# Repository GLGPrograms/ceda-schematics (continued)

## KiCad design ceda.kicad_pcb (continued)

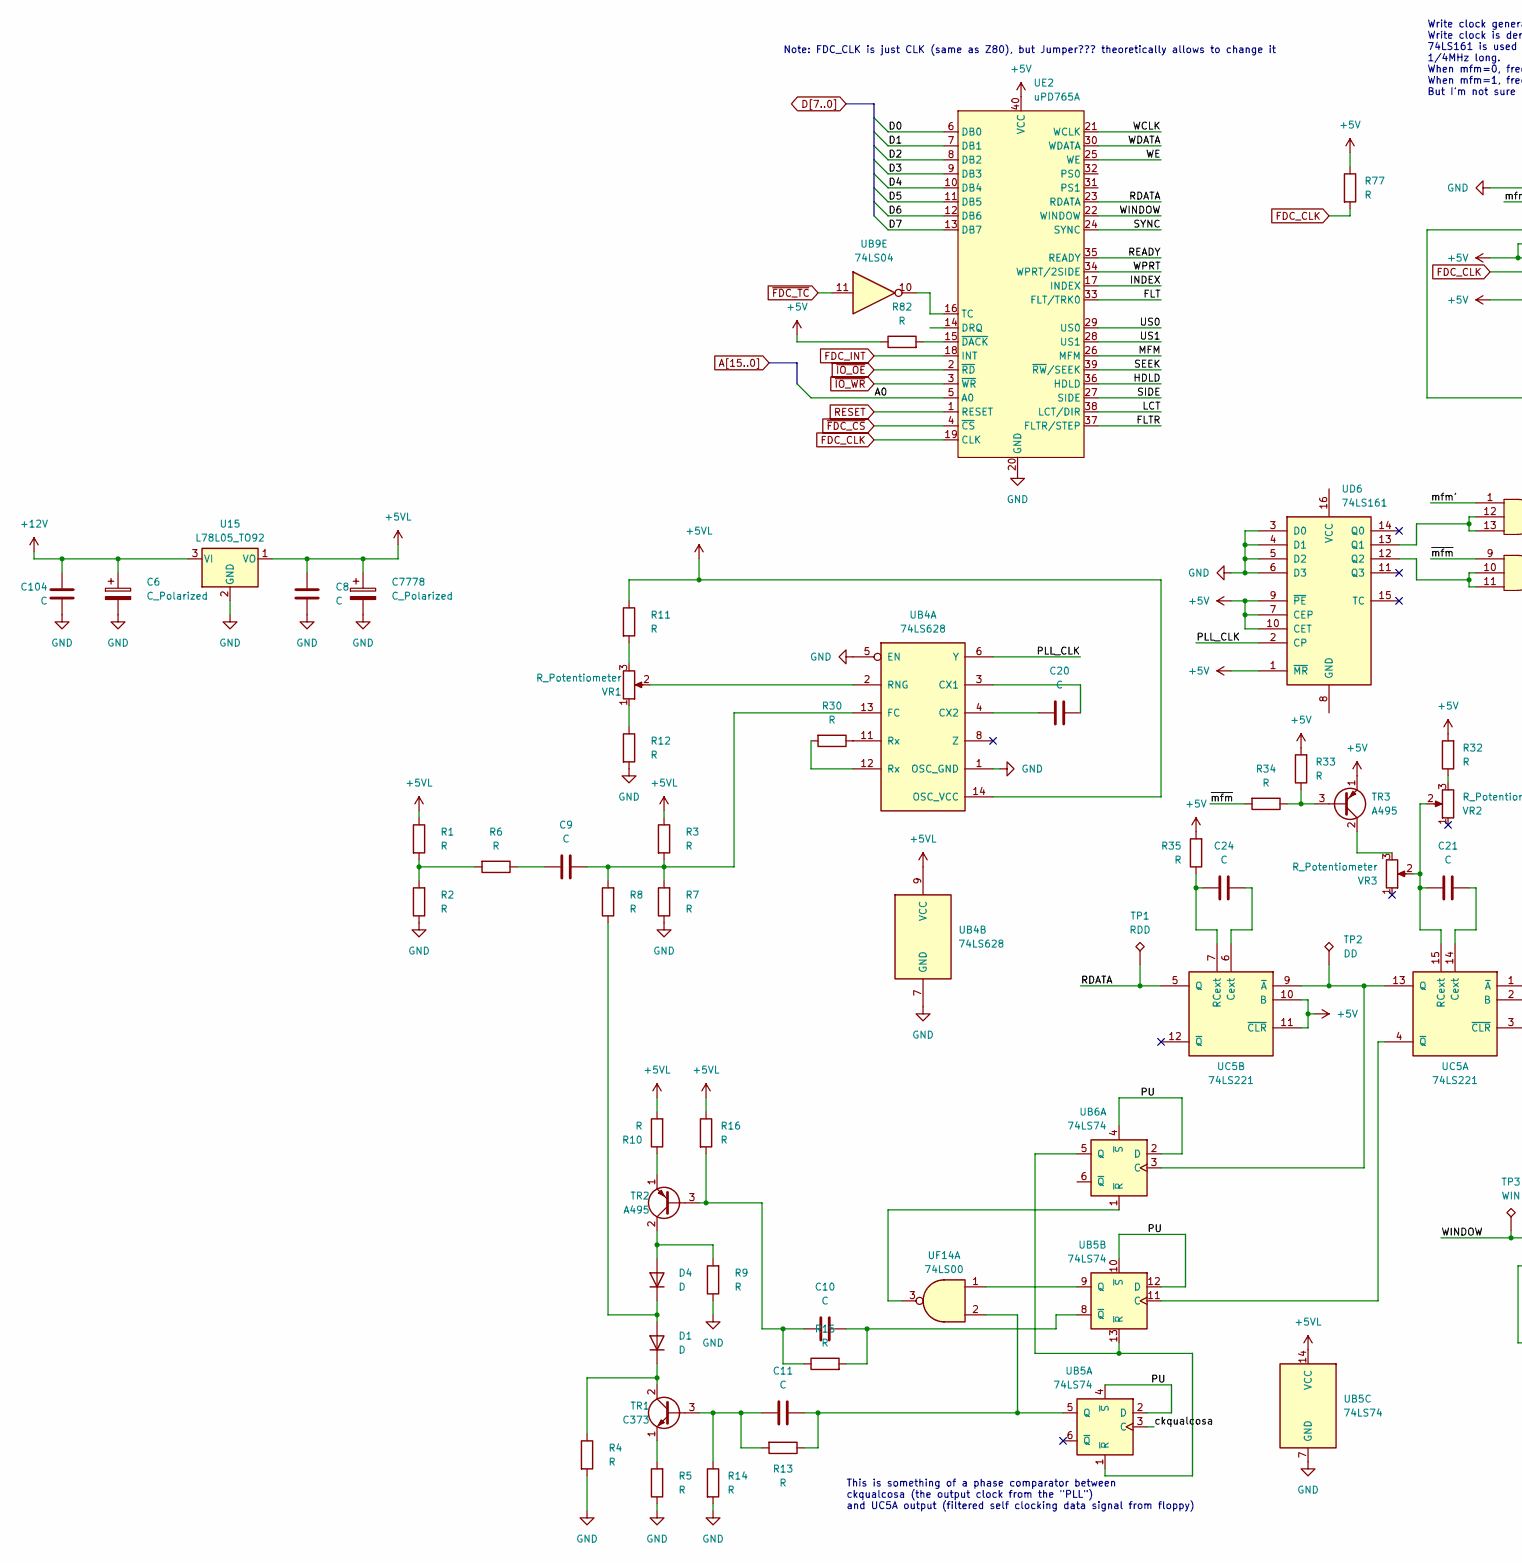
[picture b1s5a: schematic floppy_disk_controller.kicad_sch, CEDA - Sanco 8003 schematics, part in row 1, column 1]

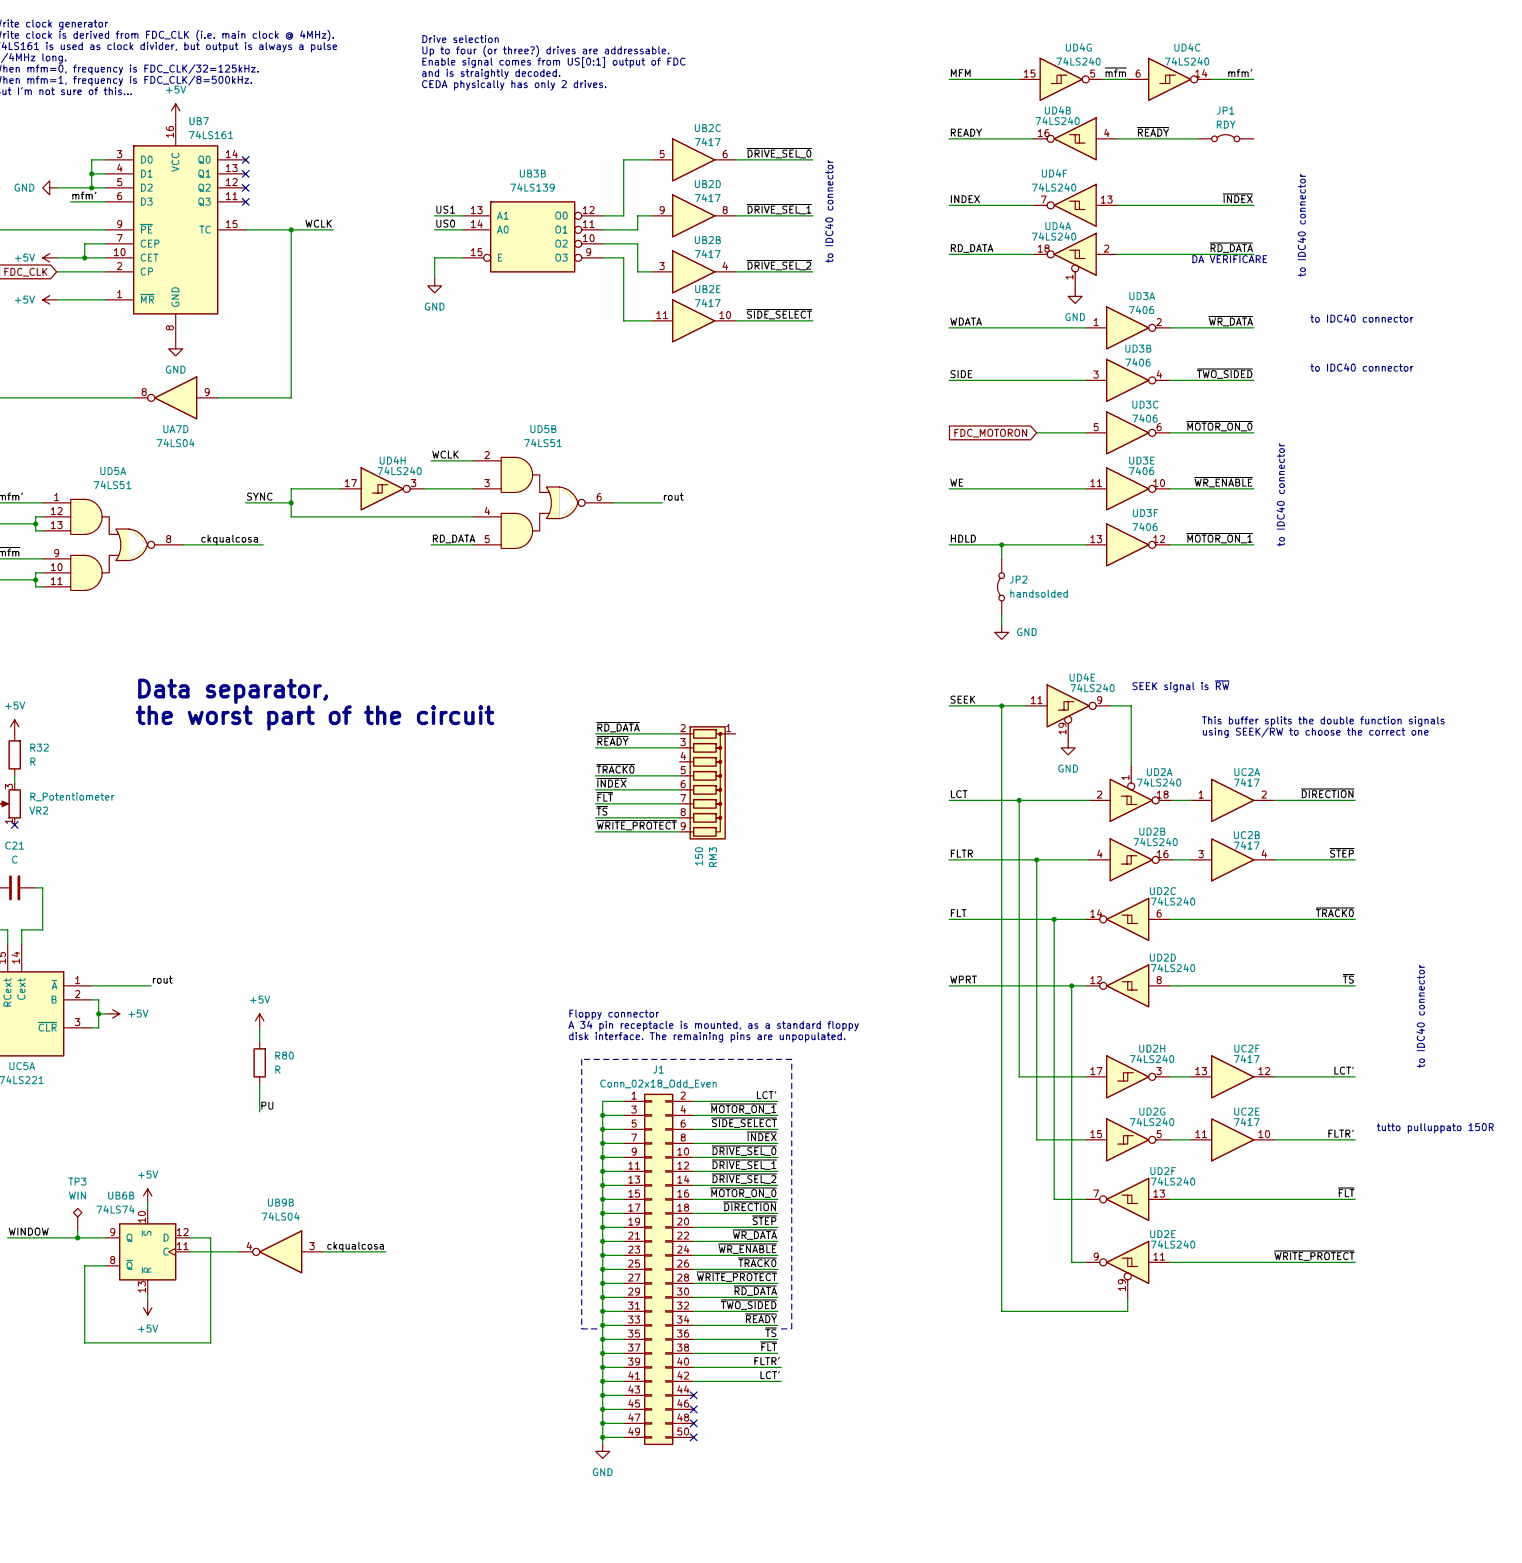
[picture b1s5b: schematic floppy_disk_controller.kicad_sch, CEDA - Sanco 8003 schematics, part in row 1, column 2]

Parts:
C6, C7778: C_Polarized; CP_Radial_D5.0mm_P2.50mm
C8, C9, C10, C11, C20, C21, C24, C104: C; C_Disc_D4.3mm_W1.9mm_P5.00mm
D1, D4: D; D_A-405_P5.08mm_Vertical_KathodeUp
J1: Conn_02x18_Odd_Even; IDC-Header_2x25_P2.54mm_Vertical
JP1: RDY; PinHeader_2x01_P2.54mm_Vertical
JP2: handsolded
R1, R2, R3, R4, R5, R6, R7, R8, R9, R10, R11, R12, R13, R14, R15, R16, R30, R32, R33, R34, R35, R80, R82: R; R_Axial_DIN0204_L3.6mm_D1.6mm_P5.08mm_Vertical
R77: R; R_Axial_DIN0309_L9.0mm_D3.2mm_P12.70mm_Horizontal
RM3: 150; R_Array_SIP9
TP1: RDD; TestPoint_Plated_Hole_D2.0mm
TP2: DD; TestPoint_Plated_Hole_D2.0mm
TP3: WIN; TestPoint_Plated_Hole_D2.0mm
TR1: C373; TO-92_Inline_Wide
TR2, TR3: A495; TO-92_Inline_Wide
U15: L78L05_TO92; TO-92_Inline_Wide
UA7: 74LS04; DIP-14_W7.62mm
UB2: 7417; DIP-14_W7.62mm
UB3: 74LS139; DIP-16_W7.62mm
UB4: 74LS628; DIP-14_W7.62mm
UB5, UB6: 74LS74; DIP-14_W7.62mm
UB7: 74LS161; DIP-16_W7.62mm
UB9: 74LS04; DIP-14_W7.62mm
UC2: 7417; DIP-14_W7.62mm
UC5: 74LS221; DIP-16_W7.62mm
UD2, UD4: 74LS240; DIP-20_W7.62mm
UD3: 7406; DIP-14_W7.62mm
UD5: 74LS51; DIP-14_W7.62mm
UD6: 74LS161; DIP-16_W7.62mm
UE2: uPD765A; DIP-40_W15.24mm
UF14: 74LS00; DIP-14_W7.62mm
VR1, VR2, VR3: R_Potentiometer; Round_Trimmer

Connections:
+5V: R32.2, R33.2, R35.2, R77.1, R80.2, R82.1, TR3.1 (E), UB6.10 (~S), UB6.13 (~R), UB7.1 (~MR), UB7.7 (CEP), UB7.10 (CET), UB7.16 (VCC), UC5.2 (B), UC5.3 (~CLR), UC5.10 (B), UC5.11 (~CLR), UD6.1 (~MR), UD6.7 (CEP), UD6.9 (~PE), UD6.10 (CET), UE2.40 (VCC); also elsewhere on the board
+5VL: C8.1, C7778.1, R1.1, R3.1, R10.2, R11.1, R16.1, U15.1 (VO), UB4.9 (VCC), UB4.14 (OSC_VCC), UB5.14 (VCC)
+12V: C6.1, C104.1, U15.3 (VI); also elsewhere on the board
/FloppyDiskController/FLT: UD2.7, UD2.14, UE2.33 (FLT/TRK0)
/FloppyDiskController/FLTR: UD2.4, UD2.15, UE2.37 (FLTR/STEP)
/FloppyDiskController/FLTR': J1.40, UC2.10
/FloppyDiskController/HDLD: JP2.2 (B), UD3.13, UE2.36 (HDLD)
/FloppyDiskController/INDEX: UD4.7, UE2.17 (INDEX)
/FloppyDiskController/LCT: UD2.2, UD2.17, UE2.38 (LCT/DIR)
/FloppyDiskController/LCT': J1.2, J1.42, UC2.12
/FloppyDiskController/MFM: UD4.15, UE2.26 (MFM)
/FloppyDiskController/PLL_CLK: UB4.6 (Y), UD6.2 (CP)
/FloppyDiskController/PU: R80.1, UB5.2 (D), UB5.4 (~S), UB5.10 (~S), UB5.12 (D), UB6.2 (D), UB6.4 (~S)
/FloppyDiskController/RDATA: TP1.1, UC5.5 (Q), UE2.23 (RDATA)
/FloppyDiskController/RD_DATA: UD4.18, UD5.5
/FloppyDiskController/READY: UD4.16, UE2.35 (READY)
/FloppyDiskController/SEEK: UD2.19, UD4.11, UE2.39 (~RW/SEEK)
/FloppyDiskController/SIDE: UD3.3, UE2.27 (SIDE)
/FloppyDiskController/SYNC: UD4.17, UD5.4, UE2.24 (SYNC)
/FloppyDiskController/US0: UB3.14 (A0), UE2.29 (US0)
/FloppyDiskController/US1: UB3.13 (A1), UE2.28 (US1)
/FloppyDiskController/WCLK: UA7.9, UB7.15 (TC), UD5.2, UE2.21 (WCLK)
/FloppyDiskController/WDATA: UD3.1, UE2.30 (WDATA)
/FloppyDiskController/WE: UD3.11, UE2.25 (WE)
/FloppyDiskController/WINDOW: TP3.1, UB6.9 (Q), UE2.22 (WINDOW)
/FloppyDiskController/WPRT: UD2.9, UD2.12, UE2.34 (WPRT/2SIDE)
/FloppyDiskController/ckqualcosa: UB5.3 (C), UB9.3, UD5.8
/FloppyDiskController/mfm': UB7.6 (D3), UD4.14, UD5.1
/FloppyDiskController/rout: UC5.1 (~A), UD5.6
/FloppyDiskController/~DIRECTION: J1.18, UC2.2
/FloppyDiskController/~DRIVE_SEL_0: J1.10, UB2.6
/FloppyDiskController/~DRIVE_SEL_1: J1.12, UB2.8
/FloppyDiskController/~DRIVE_SEL_2: J1.14, UB2.4
/FloppyDiskController/~FLT: J1.38, RM3.7 (R6), UD2.13
/FloppyDiskController/~INDEX: J1.8, RM3.6 (R5), UD4.13
/FloppyDiskController/~MOTOR_ON_0: J1.16, UD3.6
/FloppyDiskController/~MOTOR_ON_1: J1.4, UD3.12
/FloppyDiskController/~RD_DATA: J1.30, RM3.2 (R1), UD4.2
/FloppyDiskController/~READY: J1.34, JP1.1 (A), RM3.3 (R2), UD4.4
/FloppyDiskController/~SIDE_SELECT: J1.6, UB2.10
/FloppyDiskController/~STEP: J1.20, UC2.4
/FloppyDiskController/~TRACK0: J1.26, RM3.5 (R4), UD2.6
/FloppyDiskController/~TS: J1.36, RM3.8 (R7), UD2.8
/FloppyDiskController/~TWO_SIDED: J1.32, UD3.4
/FloppyDiskController/~WRITE_PROTECT: J1.28, RM3.9 (R8), UD2.11
/FloppyDiskController/~WR_DATA: J1.22, UD3.2
/FloppyDiskController/~WR_ENABLE: J1.24, UD3.10
/FloppyDiskController/~mfm: R34.2, UD4.5, UD4.6, UD5.9
A0: UE2.5 (A0); also elsewhere on the board
D0: UE2.6 (DB0); also elsewhere on the board
D1: UE2.7 (DB1); also elsewhere on the board
D2: UE2.8 (DB2); also elsewhere on the board
D3: UE2.9 (DB3); also elsewhere on the board
D4: UE2.10 (DB4); also elsewhere on the board
D5: UE2.11 (DB5); also elsewhere on the board
D6: UE2.12 (DB6); also elsewhere on the board
D7: UE2.13 (DB7); also elsewhere on the board
FDC_CLK: R77.2, UB7.2 (CP), UE2.19 (CLK); also elsewhere on the board
FDC_INT: UE2.18 (INT); also elsewhere on the board
FDC_MOTORON: UD3.5; also elsewhere on the board
GND: C6.2, C8.2, C104.2, C7778.2, J1.1, J1.3, J1.5, J1.7, J1.9, J1.11, J1.13, J1.15, J1.17, J1.19, J1.21, J1.23, J1.25, J1.27, J1.29, J1.31, J1.33, J1.35, J1.37, J1.39, J1.41, J1.43, J1.45, J1.47, J1.49, JP2.1 (A), R2.1, R4.2, R5.1, R7.1, R9.1, R12.2, R14.2, U15.2 (GND), UB3.15 (E), UB4.1 (OSC_GND), UB4.5 (EN), UB4.7 (GND), UB5.7 (GND), UB7.3 (D0), UB7.4 (D1), UB7.5 (D2), UB7.8 (GND), UD4.1, UD4.19, UD6.3 (D0), UD6.4 (D1), UD6.5 (D2), UD6.6 (D3), UE2.20 (GND); also elsewhere on the board
unnamed: C9.1, R6.1
unnamed: D1.2 (A), D4.1 (K), R8.1
unnamed: D1.1 (K), R4.1, TR1.2 (C)
unnamed: D4.2 (A), R9.2, TR2.2 (C)
unnamed: R1.2, R2.2, R6.2
unnamed: R11.2, VR1.3
unnamed: R12.1, VR1.1
unnamed: R30.1, UB4.11 (Rx)
unnamed: R30.2, UB4.12 (Rx)
unnamed: R32.1, VR2.3
unnamed: C11.1, R13.2, R14.1, TR1.3 (B)
unnamed: R5.2, TR1.1 (E)
unnamed: C10.1, R15.1, R16.2, TR2.3 (B)
unnamed: R10.1, TR2.1 (E)
unnamed: R33.1, R34.1, TR3.3 (B)
unnamed: TR3.2 (C), VR3.3
unnamed: UB2.5, UB3.12 (O0)
unnamed: UB2.9, UB3.11 (O1)
unnamed: UB2.3, UB3.10 (O2)
unnamed: UB2.11, UB3.9 (O3)
unnamed: C20.2, UB4.3 (CX1)
unnamed: C20.1, UB4.4 (CX2)
unnamed: C9.2, R3.2, R7.2, R8.2, UB4.13 (FC)
unnamed: UB4.2 (RNG), VR1.2
unnamed: C11.2, R13.1, UB5.5 (Q), UF14.2
unnamed: UB5.1 (~R), UB5.13 (~R), UB6.5 (Q)
unnamed: UB5.11 (C), UC5.4 (~Q)
unnamed: UB5.9 (Q), UF14.1
unnamed: C10.2, R15.2, UB5.8 (~Q)
unnamed: TP2.1, UB6.3 (C), UC5.9 (~A), UC5.13 (Q)
unnamed: UB6.1 (~R), UF14.3
unnamed: UB6.11 (C), UB9.4
unnamed: UB6.8 (~Q), UB6.12 (D)
unnamed: UA7.8, UB7.9 (~PE)
unnamed: UC2.1, UD2.18
unnamed: UC2.3, UD2.16
unnamed: UC2.11, UD2.5
unnamed: UC2.13, UD2.3
unnamed: C21.2, UC5.14 (Cext)
unnamed: C21.1, UC5.15 (RCext), VR2.2, VR3.2
unnamed: C24.2, UC5.6 (Cext)
unnamed: C24.1, R35.1, UC5.7 (RCext)
unnamed: UD2.1, UD4.9
unnamed: UD4.3, UD5.3
unnamed: UD5.12, UD5.13, UD6.13 (Q1)
unnamed: UD5.10, UD5.11, UD6.12 (Q2)
unnamed: UB9.10, UE2.16 (TC)
unnamed: R82.2, UE2.15 (~DACK)
RESET: UE2.1 (RESET); also elsewhere on the board
~FDC_CS: UE2.4 (~CS); also elsewhere on the board
~FDC_TC: UB9.11; also elsewhere on the board
~IO_OE: UE2.2 (~RD); also elsewhere on the board
~IO_WR: UE2.3 (~WR); also elsewhere on the board

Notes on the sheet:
to IDC40 connector
Floppy connector A 34 pin receptacle is mounted, as a standard floppy disk interface. The remaining pins are unpopulated.
tutto pulluppato 150R
DA VERIFICARE
This buffer splits the double function signals using SEEK/RW to choose the correct one
This is something of a phase comparator between ckqualcosa (the output clock from the "PLL") and UC5A output (filtered self clocking data signal from floppy)
SEEK signal is ~{RW}
Drive selection Up to four (or three?) drives are addressable. Enable signal comes from US[0:1] output of FDC and is straightly decoded. CEDA physically has only 2 drives.
Note: FDC_CLK is just CLK (same as Z80), but Jumper??? theoretically allows to change it
Data separator, the worst part of the circuit
Write clock generator Write clock is derived from FDC_CLK (i.e. main clock @ 4MHz). 74LS161 is used as clock divider, but output is always a pulse 1/4MHz long. When mfm=0, frequency is FDC_CLK/32=125kHz. When mfm=1, frequency is FDC_CLK/8=500kHz. But I'm not sure of this...

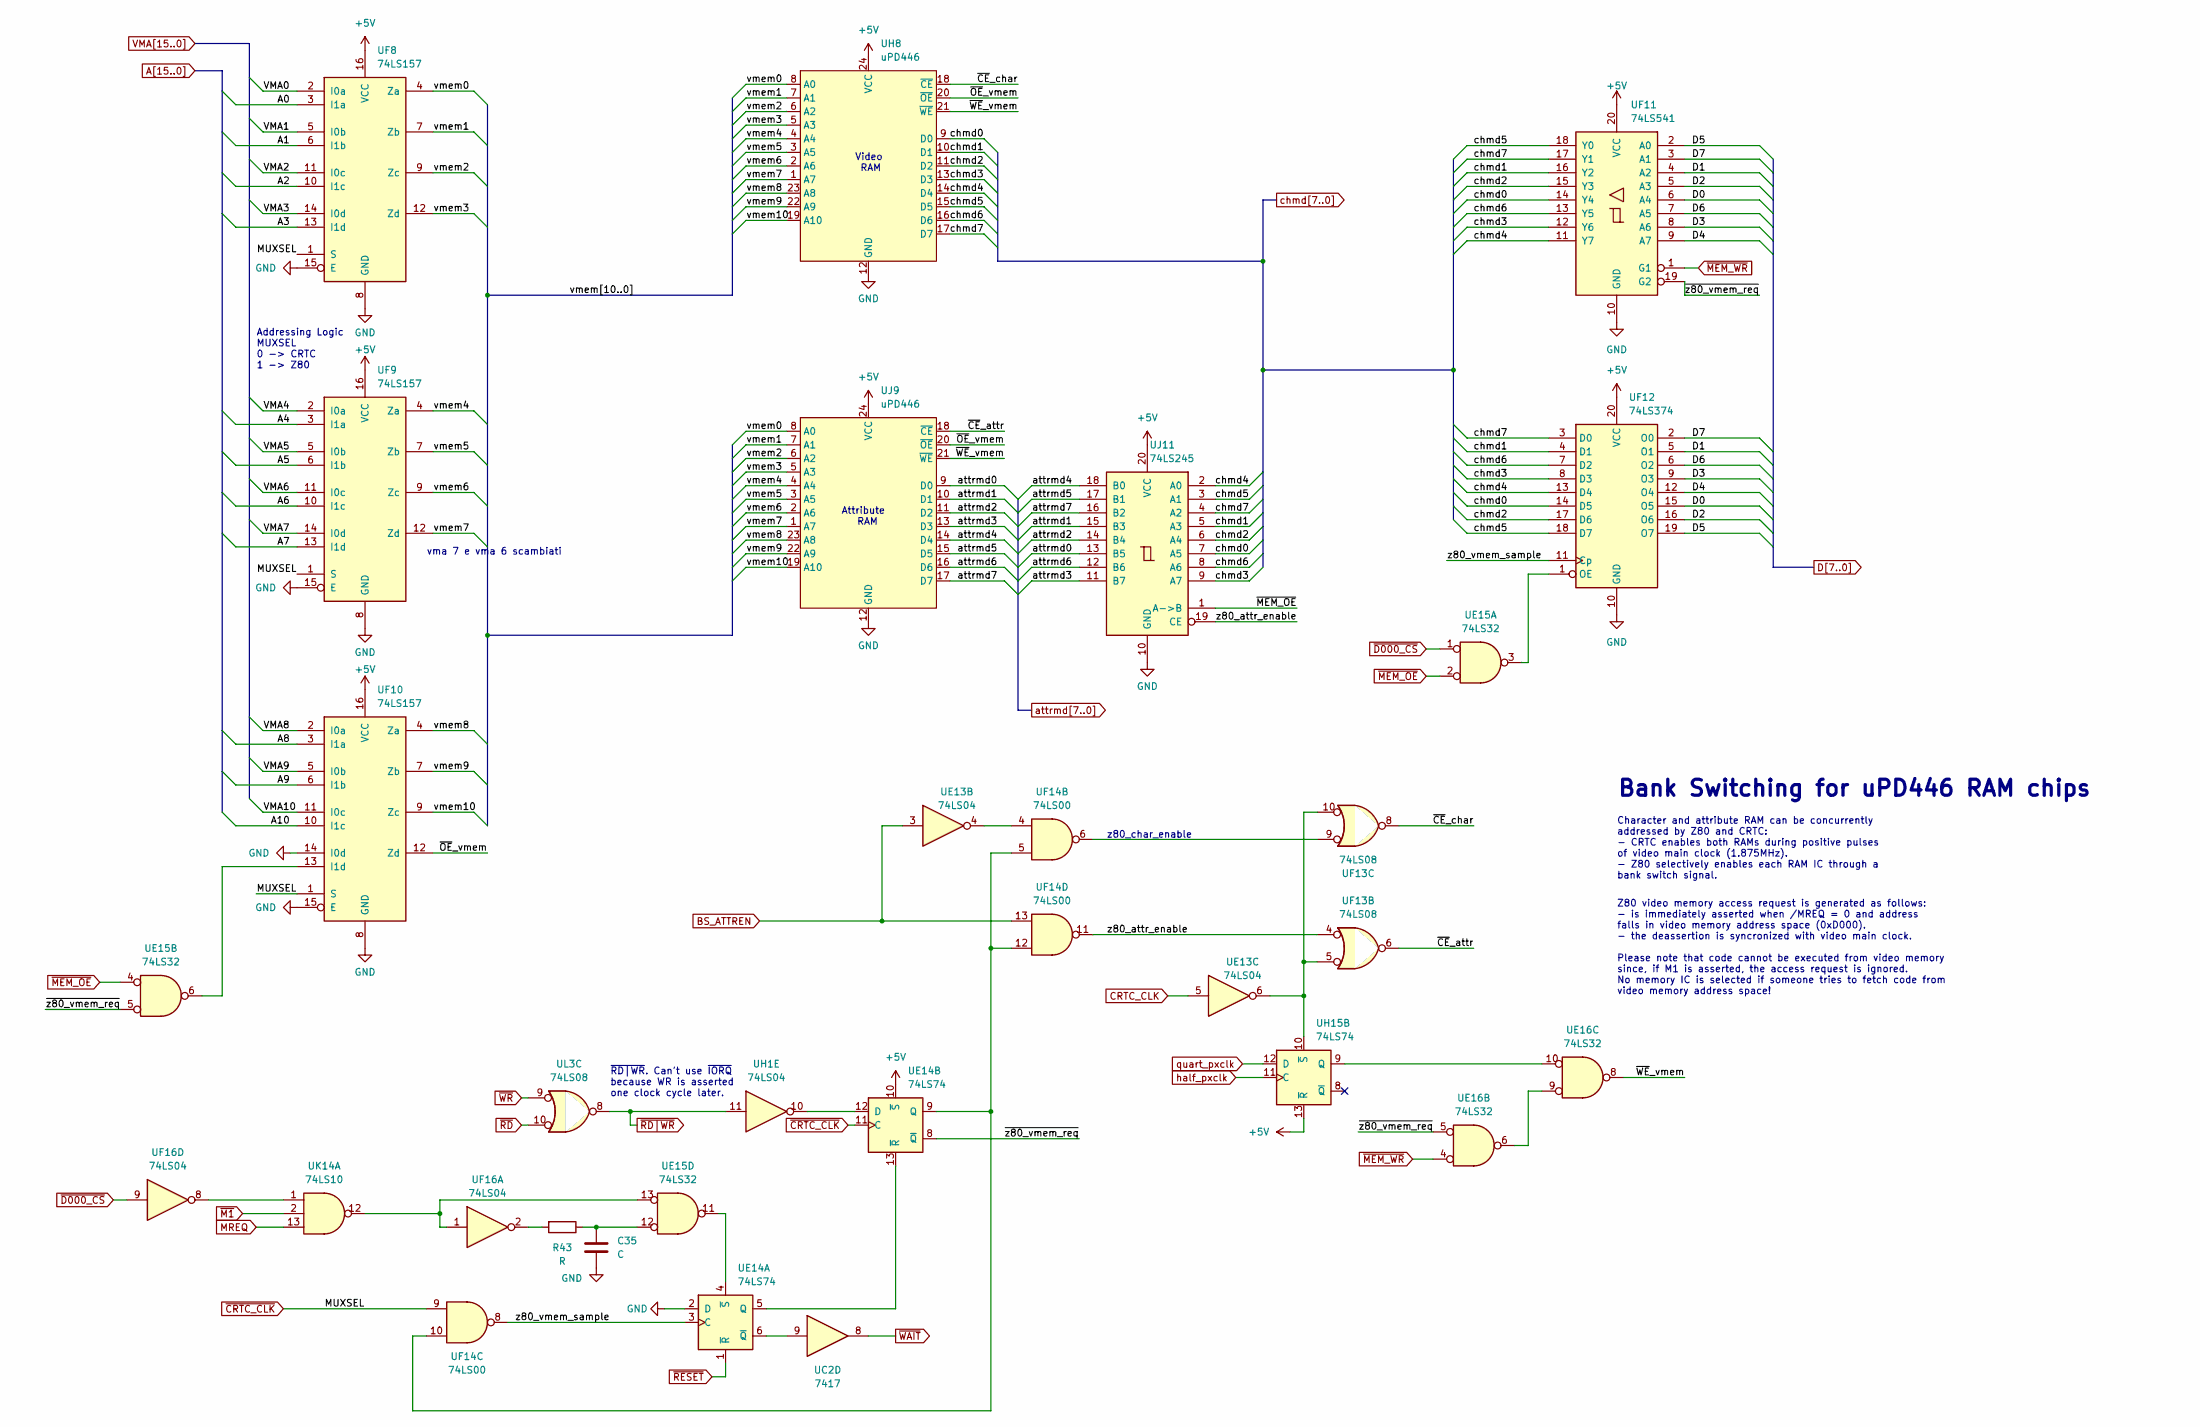
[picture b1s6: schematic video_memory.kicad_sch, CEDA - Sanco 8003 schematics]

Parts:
C35: C; C_Disc_D4.3mm_W1.9mm_P5.00mm
R43: R; R_Axial_DIN0204_L3.6mm_D1.6mm_P5.08mm_Vertical
UC2: 7417; DIP-14_W7.62mm
UE13: 74LS04; DIP-14_W7.62mm
UE14: 74LS74; DIP-14_W7.62mm
UE15, UE16: 74LS32; DIP-14_W7.62mm
UF8, UF9, UF10: 74LS157; DIP-16_W7.62mm
UF11: 74LS541; DIP-20_W7.62mm
UF12: 74LS374; DIP-20_W7.62mm
UF13: 74LS08; DIP-14_W7.62mm
UF14: 74LS00; DIP-14_W7.62mm
UF16: 74LS04; DIP-14_W7.62mm
UH1: 74LS04; DIP-14_W7.62mm
UH8: uPD446; DIP-24_W15.24mm
UH15: 74LS74; DIP-14_W7.62mm
UJ9: uPD446; DIP-24_W15.24mm
UJ11: 74LS245; DIP-20_W7.62mm
UK14: 74LS10; DIP-14_W7.62mm
UL3: 74LS08; DIP-14_W7.62mm

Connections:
+5V: UE14.10 (~S), UF8.16 (VCC), UF9.16 (VCC), UF10.16 (VCC), UF11.20 (VCC), UF12.20 (VCC), UH8.24 (VCC), UH15.13 (~R), UJ9.24 (VCC), UJ11.20 (VCC); also elsewhere on the board
/Video Memory/vmem0: UF8.4 (Za), UH8.8 (A0), UJ9.8 (A0)
/Video Memory/vmem1: UF8.7 (Zb), UH8.7 (A1), UJ9.7 (A1)
/Video Memory/vmem2: UF8.9 (Zc), UH8.6 (A2), UJ9.6 (A2)
/Video Memory/vmem3: UF8.12 (Zd), UH8.5 (A3), UJ9.5 (A3)
/Video Memory/vmem4: UF9.4 (Za), UH8.4 (A4), UJ9.4 (A4)
/Video Memory/vmem5: UF9.7 (Zb), UH8.3 (A5), UJ9.3 (A5)
/Video Memory/vmem6: UF9.9 (Zc), UH8.2 (A6), UJ9.2 (A6)
/Video Memory/vmem7: UF9.12 (Zd), UH8.1 (A7), UJ9.1 (A7)
/Video Memory/vmem8: UF10.4 (Za), UH8.23 (A8), UJ9.23 (A8)
/Video Memory/vmem9: UF10.7 (Zb), UH8.22 (A9), UJ9.22 (A9)
/Video Memory/vmem10: UF10.9 (Zc), UH8.19 (A10), UJ9.19 (A10)
/Video Memory/z80_attr_enable: UF13.4, UF14.11, UJ11.19 (CE)
/Video Memory/z80_vmem_sample: UE14.3 (C), UF12.11 (Cp), UF14.8
/Video Memory/~CE_attr: UF13.6, UJ9.18 (~CE)
/Video Memory/~CE_char: UF13.8, UH8.18 (~CE)
/Video Memory/~OE_vmem: UF10.12 (Zd), UH8.20 (~OE), UJ9.20 (~OE)
/Video Memory/~WE_vmem: UE16.8, UH8.21 (~WE), UJ9.21 (~WE)
/Video Memory/~z80_vmem_req: UE14.8 (~Q), UE15.5, UE16.5, UF11.19 (G2)
A0: UF8.3 (I1a); also elsewhere on the board
A1: UF8.6 (I1b); also elsewhere on the board
A2: UF8.10 (I1c); also elsewhere on the board
A3: UF8.13 (I1d); also elsewhere on the board
A4: UF9.3 (I1a); also elsewhere on the board
A5: UF9.6 (I1b); also elsewhere on the board
A6: UF9.10 (I1c); also elsewhere on the board
A7: UF9.13 (I1d); also elsewhere on the board
A8: UF10.3 (I1a); also elsewhere on the board
A9: UF10.6 (I1b); also elsewhere on the board
A10: UF10.10 (I1c); also elsewhere on the board
BS_ATTREN: UE13.3, UF14.13; also elsewhere on the board
CRTC_CLK: UE13.5; also elsewhere on the board
D0: UF11.6 (A4), UF12.15 (O5); also elsewhere on the board
D1: UF11.4 (A2), UF12.5 (O1); also elsewhere on the board
D2: UF11.5 (A3), UF12.16 (O6); also elsewhere on the board
D3: UF11.8 (A6), UF12.9 (O3); also elsewhere on the board
D4: UF11.9 (A7), UF12.12 (O4); also elsewhere on the board
D5: UF11.2 (A0), UF12.19 (O7); also elsewhere on the board
D6: UF11.7 (A5), UF12.6 (O2); also elsewhere on the board
D7: UF11.3 (A1), UF12.2 (O0); also elsewhere on the board
GND: C35.2, UE14.2 (D), UF8.8 (GND), UF8.15 (E), UF9.8 (GND), UF9.15 (E), UF10.8 (GND), UF10.14 (I0d), UF10.15 (E), UF11.10 (GND), UF12.10 (GND), UH8.12 (GND), UJ9.12 (GND), UJ11.10 (GND); also elsewhere on the board
MREQ: UK14.13; also elsewhere on the board
unnamed: C35.1, R43.1, UE15.12
unnamed: R43.2, UF16.2
unnamed: UE13.4, UF14.4
unnamed: UE14.5 (Q), UE14.13 (~R)
unnamed: UC2.9, UE14.6 (~Q)
unnamed: UE14.4 (~S), UE15.11
unnamed: UE14.12 (D), UH1.10
unnamed: UE14.9 (Q), UF14.5, UF14.10, UF14.12
unnamed: UE15.13, UF16.1, UK14.12
unnamed: UE16.6, UE16.9
unnamed: UE15.6, UF10.13 (I1d)
unnamed: UE15.3, UF12.1 (OE)
unnamed: UF13.9, UF14.6
unnamed: UF16.8, UK14.1
unnamed: UE16.10, UH15.9 (Q)
unnamed: UE13.6, UF13.5, UF13.10, UH15.10 (~S)
VMA0: UF8.2 (I0a); also elsewhere on the board
VMA1: UF8.5 (I0b); also elsewhere on the board
VMA2: UF8.11 (I0c); also elsewhere on the board
VMA3: UF8.14 (I0d); also elsewhere on the board
VMA4: UF9.2 (I0a); also elsewhere on the board
VMA5: UF9.5 (I0b); also elsewhere on the board
VMA6: UF9.11 (I0c); also elsewhere on the board
VMA7: UF9.14 (I0d); also elsewhere on the board
VMA8: UF10.2 (I0a); also elsewhere on the board
VMA9: UF10.5 (I0b); also elsewhere on the board
VMA10: UF10.11 (I0c); also elsewhere on the board
attrmd0: UJ9.9 (D0), UJ11.13 (B5); also elsewhere on the board
attrmd1: UJ9.10 (D1), UJ11.15 (B3); also elsewhere on the board
attrmd2: UJ9.11 (D2), UJ11.14 (B4); also elsewhere on the board
attrmd3: UJ9.13 (D3), UJ11.11 (B7); also elsewhere on the board
attrmd4: UJ9.14 (D4), UJ11.18 (B0); also elsewhere on the board
attrmd5: UJ9.15 (D5), UJ11.17 (B1); also elsewhere on the board
attrmd6: UJ9.16 (D6), UJ11.12 (B6); also elsewhere on the board
attrmd7: UJ9.17 (D7), UJ11.16 (B2); also elsewhere on the board
chmd0: UF11.14 (Y4), UF12.14 (D5), UH8.9 (D0), UJ11.7 (A5); also elsewhere on the board
chmd1: UF11.16 (Y2), UF12.4 (D1), UH8.10 (D1), UJ11.5 (A3); also elsewhere on the board
chmd2: UF11.15 (Y3), UF12.17 (D6), UH8.11 (D2), UJ11.6 (A4); also elsewhere on the board
chmd3: UF11.12 (Y6), UF12.8 (D3), UH8.13 (D3), UJ11.9 (A7); also elsewhere on the board
chmd4: UF11.11 (Y7), UF12.13 (D4), UH8.14 (D4), UJ11.2 (A0); also elsewhere on the board
chmd5: UF11.18 (Y0), UF12.18 (D7), UH8.15 (D5), UJ11.3 (A1); also elsewhere on the board
chmd6: UF11.13 (Y5), UF12.7 (D2), UH8.16 (D6), UJ11.8 (A6); also elsewhere on the board
chmd7: UF11.17 (Y1), UF12.3 (D0), UH8.17 (D7), UJ11.4 (A2); also elsewhere on the board
half_pxclk: UH15.11 (C); also elsewhere on the board
quart_pxclk: UH15.12 (D); also elsewhere on the board
~CRTC_CLK: UE14.11 (C), UF8.1 (S), UF9.1 (S), UF10.1 (S), UF14.9; also elsewhere on the board
~D000_CS: UE15.1, UF16.9; also elsewhere on the board
~M1: UK14.2; also elsewhere on the board
~MEM_OE: UE15.2, UE15.4, UJ11.1 (A->B); also elsewhere on the board
~MEM_WR: UE16.4, UF11.1 (G1); also elsewhere on the board
~RD|WR: UH1.11, UL3.8; also elsewhere on the board
~RD: UL3.10; also elsewhere on the board
~RESET: UE14.1 (~R); also elsewhere on the board
~WAIT: UC2.8; also elsewhere on the board
~WR: UL3.9; also elsewhere on the board

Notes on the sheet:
Attribute RAM
Character and attribute RAM can be concurrently addressed by Z80 and CRTC: - CRTC enables both RAMs during positive pulses of video main clock (1.875MHz). - Z80 selectively enables each RAM IC through a bank switch signal.
Bank Switching for uPD446 RAM chips
~{RD|WR}. Can't use ~{IORQ} because WR is asserted one clock cycle later.
z80_char_enable
vma 7 e vma 6 scambiati
Addressing Logic MUXSEL 0 -> CRTC 1 -> Z80
Z80 video memory access request is generated as follows: - is immediately asserted when /MREQ = 0 and address falls in video memory address space (0xD000). - the deassertion is syncronized with video main clock. Please note that code cannot be executed from video memory since, if M1 is asserted, th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
Video RAM

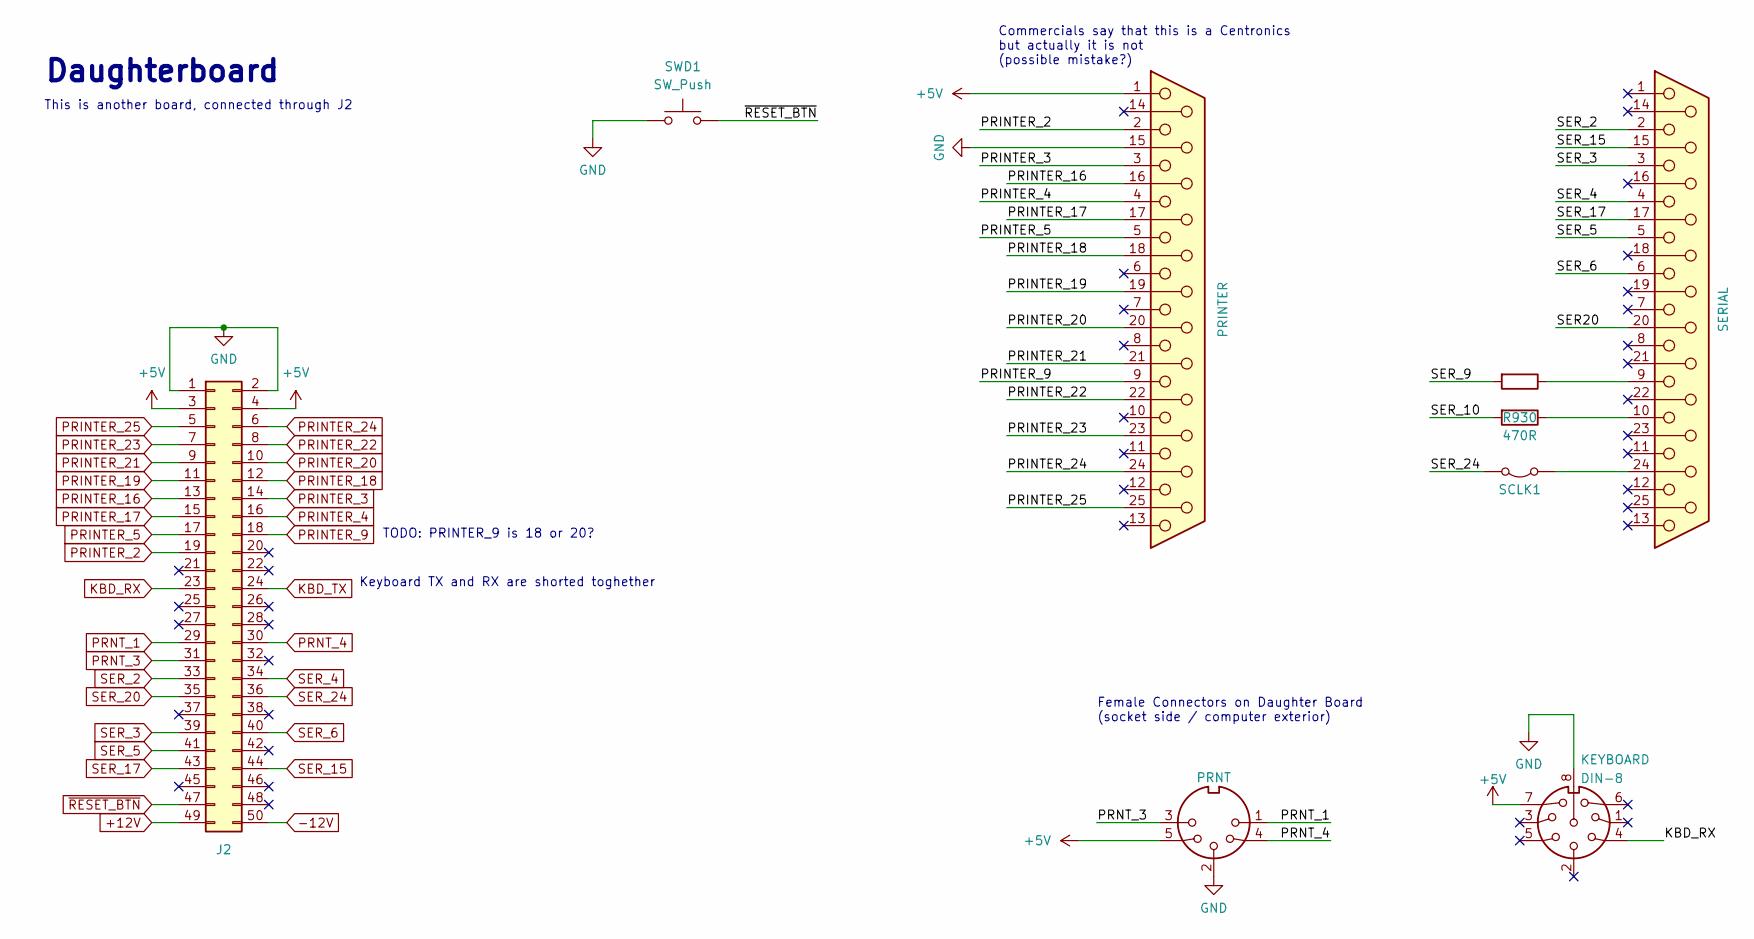
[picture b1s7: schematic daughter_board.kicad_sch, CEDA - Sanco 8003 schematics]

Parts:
J2: Conn_02x25_Odd_Even; PinHeader_2x25_P2.54mm_Vertical
KEYBOARD1: DIN-8
PRINTER1: PRINTER
PRNT1: DIN-5_180degree
R23, R930: 470R
SCLK1: Jumper_2_Bridged
SERIAL1: DB25_Female
SWD1: SW_Push

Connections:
+5V: J2.3, J2.4, KEYBOARD1.7, PRINTER1.1, PRNT1.5; also elsewhere on the board
+12V: J2.49; also elsewhere on the board
-12V: J2.50; also elsewhere on the board
GND: J2.1, J2.2, KEYBOARD1.8, PRINTER1.15, PRNT1.2, SWD1.2; also elsewhere on the board
KBD_RX: J2.23; also elsewhere on the board
KBD_TX: J2.24; also elsewhere on the board
unnamed: R23.1, SERIAL1.9
unnamed: R930.1, SERIAL1.10
unnamed: SCLK1.1 (A), SERIAL1.24
PRINTER_2: J2.19; also elsewhere on the board
PRINTER_3: J2.14; also elsewhere on the board
PRINTER_4: J2.16; also elsewhere on the board
PRINTER_5: J2.17; also elsewhere on the board
PRINTER_9: J2.18; also elsewhere on the board
PRINTER_16: J2.13; also elsewhere on the board
PRINTER_17: J2.15; also elsewhere on the board
PRINTER_18: J2.12; also elsewhere on the board
PRINTER_19: J2.11; also elsewhere on the board
PRINTER_20: J2.10; also elsewhere on the board
PRINTER_21: J2.9; also elsewhere on the board
PRINTER_22: J2.8; also elsewhere on the board
PRINTER_23: J2.7; also elsewhere on the board
PRINTER_24: J2.6; also elsewhere on the board
PRINTER_25: J2.5; also elsewhere on the board
PRNT_1: J2.29; also elsewhere on the board
PRNT_3: J2.31; also elsewhere on the board
PRNT_4: J2.30; also elsewhere on the board
SER_2: J2.33; also elsewhere on the board
SER_3: J2.39; also elsewhere on the board
SER_4: J2.34; also elsewhere on the board
SER_5: J2.41; also elsewhere on the board
SER_6: J2.40; also elsewhere on the board
SER_15: J2.44; also elsewhere on the board
SER_17: J2.43; also elsewhere on the board
SER_20: J2.35; also elsewhere on the board
SER_24: J2.36; also elsewhere on the board
~RESET_BTN: J2.47; also elsewhere on the board

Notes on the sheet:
Daughterboard
Keyboard TX and RX are shorted toghether
Female Connectors on Daughter Board (socket side / computer exterior)
TODO: PRINTER_9 is 18 or 20?
This is another board, connected through J2
Commercials say that this is a Centronics but actually it is not (possible mistake?)

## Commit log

2022-05-22 First commit.
2022-05-22 Add LICENSE.
2022-05-22 CEDA symbol library: CRTC and uPD446.
2022-05-23 Moved keyboard circuit in its sheet
2022-05-29 Video generation: video memory, character ROM and dot pattern generation.
2022-05-29 28L22 confirmed glue logic. Address selection mux trio. Pixel clock.
2022-05-29 Add test point.
2022-06-12 Recovered IO component numbering lost in old commit
2022-06-12 Added symbol for Z8440/2 (SIO/2)
2022-06-12 Added SIO in schematics
2022-06-12 Added pin numbering to SIO
2022-06-12 Fixed SIO reference in schematic
2022-06-13 Added symbols for uPD8255, Z80-CTC and uPD765A
2022-10-08 Add speaker multivibrator and address decoding logic.
2022-10-08 Add Z80 CPU draft.
2022-10-08 Update main project files.
2023-02-18 Add README.md
2023-02-19 Add SIOCLK jumper detail jumper details.
2023-02-23 Correction in speaker address annotation
2023-02-23 README: PCB model from silk screen
2023-02-23 Fix grid aligment for SIO symbol.
2023-02-23 Add address wires for SIO.
2023-02-24 Specialize generic IO sheet to SIO (serial) related.
2023-02-24 Add GPIO uPD8255 wiring for bank switching.
2023-02-24 Embed new sheets and fix symbols.
2023-02-26 Add daughterboard schematics.
2023-02-27 Add PDF export script.
2023-03-05 Some steps in bank switching and crtc circuits
    - crtc pixel clock generator
    - 2k ram, enabling logic (heavily incomplete)
    - other 2k ram, annotation regarding data bus
2023-03-13 Removed GPL license, since this is not an original work but a reverse engineering.
2023-04-13 Added bus buffers (or their placeholders) to z80cpu schematic
2023-04-13 Added address signals from Z80 to video memory
2023-04-13 Video memory bus and connections to Z80
2023-04-28 Some changes, unfortunately merged with upgrade to kicad v7
2023-04-28 Upgraded to kicad 7
2023-04-28 Fixed address connection from Z80 to buffers
2023-04-28 Note in pixel shift register
2023-04-28 Added memory management sheet with ROM/RAM addressing mux
2023-04-30 Fixed addr order in mem mux, busack on z80 buffers
2023-05-01 Small notes
2023-05-04 Found both ROM CE and OE
2023-05-04 Found aux ram CS too. A great discover...
2023-05-06 Found WR signal and fixed RD
2023-05-08 Z80 halt controls the RUN LED
2023-05-14 RAM addressing, including DRAM ras and cas
2023-05-14 Partial signal renaming
2023-05-15 Missing signal in DRAM logic
2023-05-16 Add GitHub Action to export as PDF
2023-05-17 DRAM: row/column mux, parity generator (partial), memory ICs
2023-05-21 Notes and minor fixes
2023-06-17 Discovered bank 0 + fixed wrong signals in video gen
2023-07-06 (WIP) A long job in analog video output
    ! Read comments inside video_memory_management sheet for more
    informations.
    - Completed path between dot pattern output of character shift register
    and beam output transistor.
    - Found behavior of video attribute signals: blink, underline, stretch,
    hide.
2023-07-06 (WIP) Other steps in video generation
    - Some notes regarding video attributes.
    - Found some stuck-at inputs.
2023-07-06 (WIP) Video memory concurrency
    - bank7 selector to address video or attribute RAM
    - found read and write data paths leading to video RAMs (F11, F12).
    - video RAMs CS generation.
2023-10-02 A long job in analog video output
    ! Read comments inside video_memory_management sheet for more
    informations.
    - Completed path between dot pattern output of character shift register
    and beam output transistor.
    - Found behavior of video attribute signals: blink, underline, stretch,
    hide.
2023-10-02 Other steps in video generation
    - Some notes regarding video attributes.
    - Found some stuck-at inputs.
2023-10-02 Video memory concurrency
    - bank7 selector to address video or attribute RAM
    - found read and write data paths leading to video RAMs (F11, F12).
    - video RAMs CS generation.
2023-10-02 Added some missing labels and references
2023-10-02 IO addressing space multiplexing and small IO description
2023-10-02 Serial communication interface
2023-10-02 Reset circuit
2023-10-02 Added FDC sheet (WIP), added partial parallel port inout
2023-10-02 CTC, serial clock and main clock
2023-10-02 Discovered WE and OE signals for video memories, plus others
2023-10-02 parallel port, which is absolutely not a centronics port
2023-10-02 Found vsync frame signal for z80 + minors
2023-10-02 Something else in video generation sheet
2023-10-02 Schematics refactoring:
    - New sheet reserved to video memory.
    - Removed video memory parts inside video_generation.
    - Removed video memory parts inside GPIO.
    - Generic cleanup to keep all circuits inside each sheet.
2023-10-02 Removed some dangling notes
2023-10-08 MainMemoryManagement: wire renaming
2023-10-08 video gen and memory: wire renaming, but something is still missing
2023-10-08 Moved clock circuit in the clock/reset sheet
2023-10-08 GPIO: wire renaming
2023-10-08 IO space: wire renaming
2023-10-08 Serial: wire renaming
2023-10-08 Z80 and reset/clock: wire naming
2023-10-08 DRAM: wire renaming
2023-10-09 Typo fixes
2023-10-09 Daughterboard
2023-10-24 Fixed typo in video generation. Added some useful (I hope) notes.
2023-10-26 Graphical error: 7417 is a non-inverting buffer
2023-11-03 Components renaming according to the Uxy convention.
2023-11-03 VCC -> +5V
2023-11-03 Minor fixes
2023-11-05 Edited some notes
2023-11-24 Notes in kicad's sheet text blocks
2023-12-11 FDC: added missing TC wire from small IO to FDC
2023-12-23 CTC: added missing sheet
2025-08-17 Upgrade to KiCAD 9.0
2025-08-25 drc: updated symbols
2025-08-25 drc: corrections in net names
2025-08-25 drc: fixed labels
2025-08-25 Annotated all components
2025-08-25 Assigned default footprints to ICs
2025-09-14 Fixed packages
2025-09-14 Fixed some wrong labels
2025-09-14 Missing global label "dram_addr_sel"
2025-09-14 Fixed wrong labels and connections, added footprint for dip switch
2025-09-14 Renamed conflicting resistors in FDC
    R1xx are randomly assigned just to avoid conflicts with following commit
2025-09-14 Fixed label PERROR
2025-09-14 Fixed missing resistors in dram addresses
    TODO: check their values on the actual PCB
2025-09-14 pcb: first commit
2025-09-14 pcb: added some more traces
2025-09-22 Corrected MEM_OE and MREQ labels
2025-09-24 pcb: added more traces
2025-09-26 fdc: wrong component removed
2025-09-30 pcb: finished IC routing
2025-10-14 pcb: added and placed almost all components
2025-10-14 pcb: fixed position of first IC column
2025-10-18 pcb: fixed pin order of RM5
2025-10-18 sch: fixed fdc connections according to actual measurements on pcb
2025-10-19 pcb: added all the connector, 99% routed
2025-10-19 pcb: cleaned traces removing some of the graphical errors
2025-10-20 pcb and sch: finished routing and fixing connections
    There are still some minor inconsistencies (/WR, /RD, one PRINTER
    signal), some passives missing (decoupling caps, power stage), but the
    schematic and the pcb should be more or less complete.
2025-10-23 sch: fixed fdc rd/wr signals, ported in pcb too
2025-10-23 sch: +12v in daughterboard connector
2025-10-24 pcb: fixed traces
2025-10-27 pcb: added power in caps, reordered ref no, fixed power traces
2025-10-27 sch: added pin 1 to DRAM, pulled up
2025-10-27 pcb: proper symbols for MAP and MAINCLK
